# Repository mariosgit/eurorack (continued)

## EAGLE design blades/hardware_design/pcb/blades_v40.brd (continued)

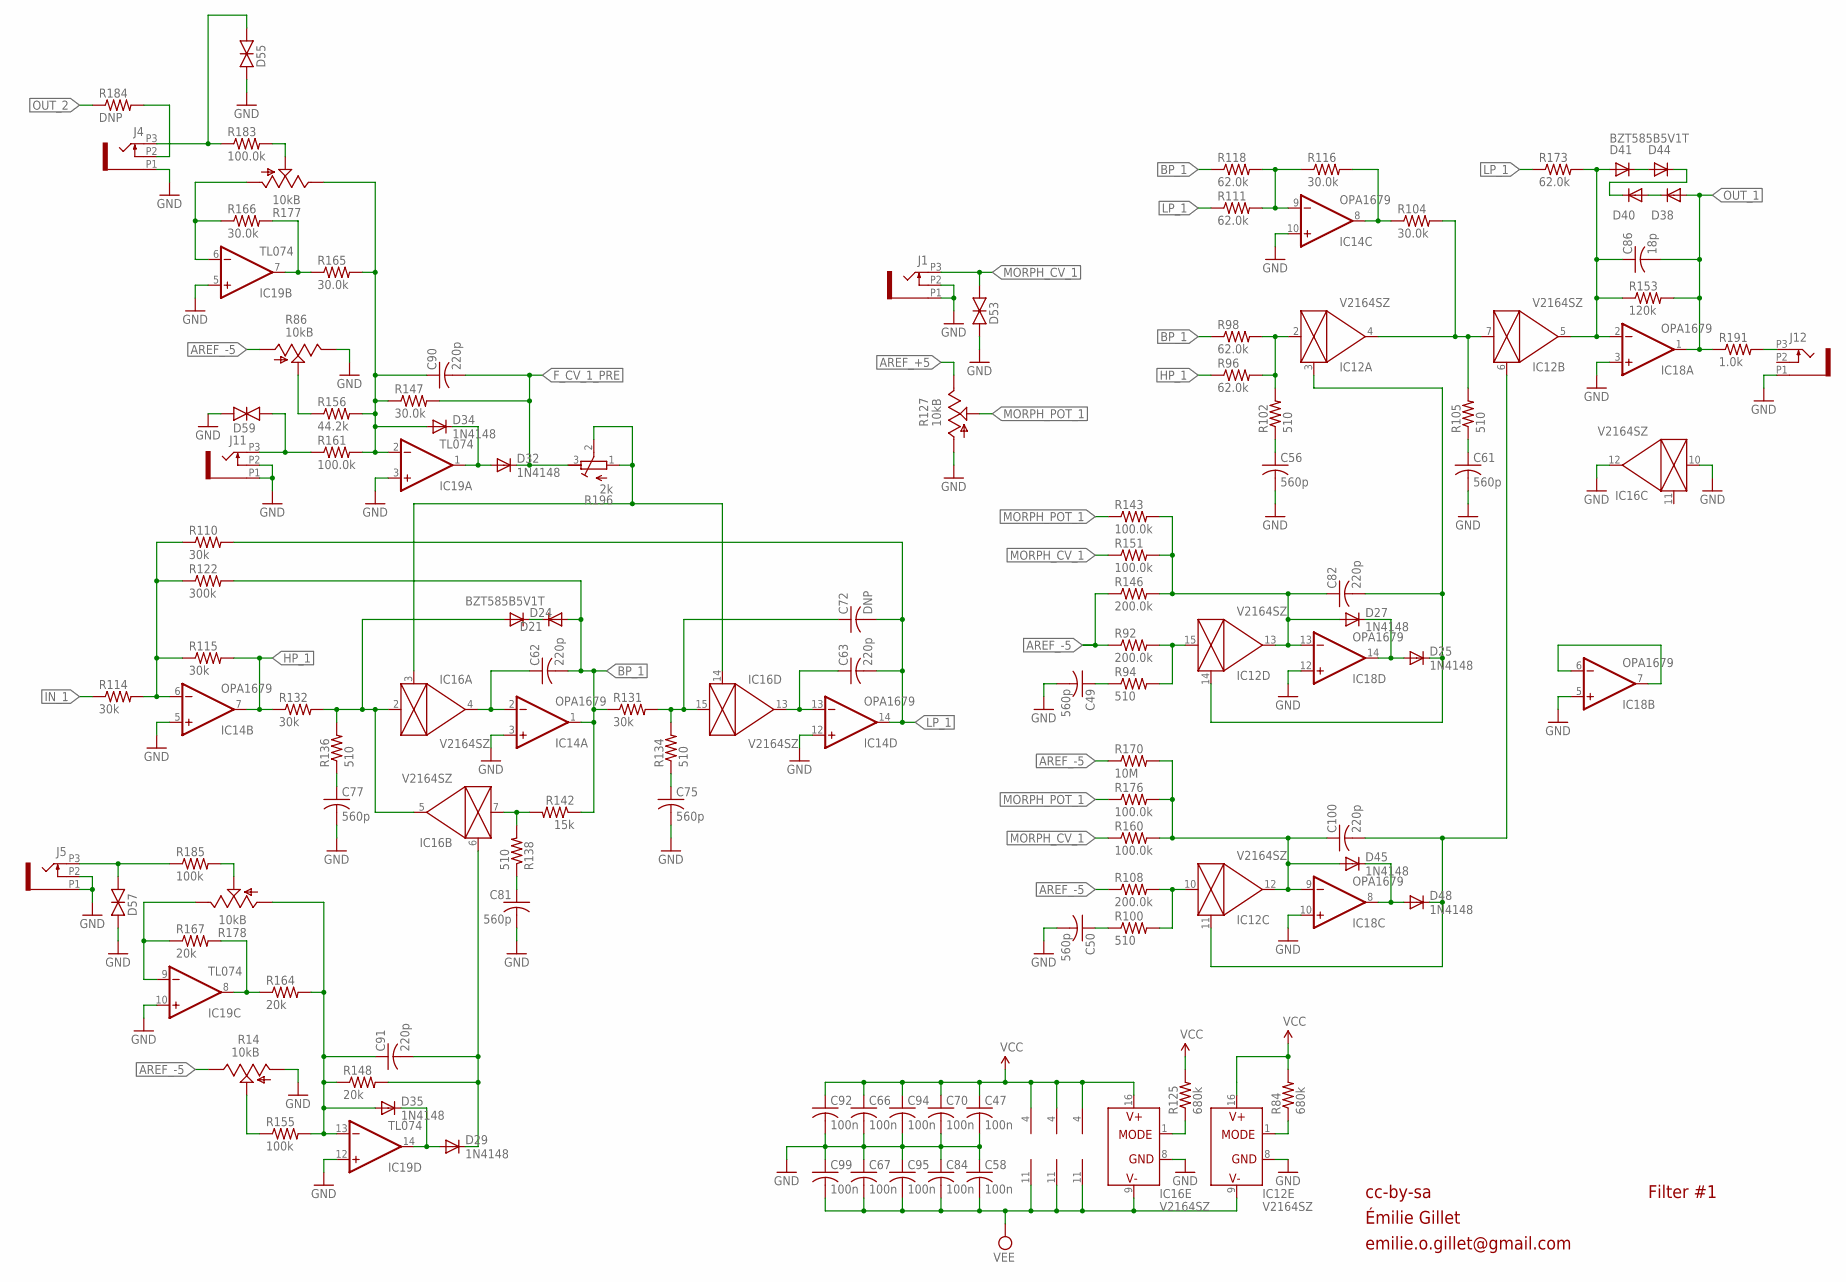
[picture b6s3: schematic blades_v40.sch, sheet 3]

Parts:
C47, C58, C66, C67, C70, C84, C92, C94, C95, C99: 100n; C0402
C49, C50, C56, C61, C75, C77, C81: 560p; C0402
C62, C63, C82, C90, C91, C100: 220p; C0402
C72: DNP; C0402
C86: 18p; C0402
D21, D24, D38, D40, D41, D44: BZT585B5V1T; SOD523
D25, D27, D29, D32, D34, D35, D45, D48: 1N4148; SOD523
D53, D55, D57, D59: TVS; 0603
IC12, IC16: V2164SZ; SOIC16N
IC14, IC18: OPA1679; TSSOP14_065
IC19: TL074; TSSOP14_065
J1, J4, J5, J11, J12: PJ301_THONKICONNTME; WQP_PJ_301M_TME
R14, R86, R127: 10kB; ALPS_POT_VERTICAL_PS
R84, R125: 680k; R0402
R92, R108, R146: 200.0k; R0402
R94, R100, R102, R105, R134, R136, R138: 510; R0402
R96, R98, R111, R118, R173: 62.0k; R0402
R104, R116, R147, R165, R166: 30.0k; R0402
R110, R114, R115, R131, R132: 30k; R0402
R122: 300k; R0402
R142: 15k; R0402
R143, R151, R160, R161, R176, R183: 100.0k; R0402
R148, R164, R167: 20k; R0402
R153: 120k; R0402
R155, R185: 100k; R0402
R156: 44.2k; R0402
R170: 10M; R0402
R177, R178: 10kB; ALPS_POT_NARROW
R184: DNP; R0603
R191: 1.0k; R0603
R196: 2k; RTRIM3296W

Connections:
AREF_+5: R127.P$1 (E); also elsewhere on the board
AREF_-5: R14.P$1 (E), R86.P$3 (A), R92.1, R108.1, R146.1, R170.1; also elsewhere on the board
BP_1: C62.2, D21.A, IC14.1 (OUT), R98.1, R118.1, R122.2, R131.1, R142.1
F_CV_1: IC16.3 (CTRL), IC16.14 (CTRL), R196.1 (E), R196.2 (S)
F_CV_1_PRE: C90.2, D32.C, R147.2, R196.3 (A); also elsewhere on the board
GND: C47.2, C49.2, C50.2, C56.2, C58.1, C61.2, C66.2, C67.1, C70.2, C75.2, C77.2, C81.2, C84.1, C92.2, C94.2, C95.1, C99.1, D53.1 (A), D55.1 (A), D57.1 (A), D59.1 (A), IC12.8 (GND), IC14.3 (+IN), IC14.5 (+IN), IC14.10 (+IN), IC14.12 (+IN), IC16.8 (GND), IC16.10 (IN), IC16.12 (OUT), IC18.3 (+IN), IC18.5 (+IN), IC18.10 (+IN), IC18.12 (+IN), IC19.3 (+IN), IC19.5 (+IN), IC19.10 (+IN), IC19.12 (+IN), J1.P1 (1), J1.P2 (2), J4.P1 (1), J5.P1 (1), J5.P2 (2), J11.P1 (1), J11.P2 (2), J12.P1 (1), R14.P$3 (A), R86.P$1 (E), R127.P$3 (A); also elsewhere on the board
HP_1: IC14.7 (OUT), R96.1, R115.2, R132.1
IN_1: R114.1; also elsewhere on the board
LP_1: C63.2, C72.2, IC14.14 (OUT), R110.2, R111.1, R173.1
MORPH_1A: C82.2, D25.C, IC12.3 (CTRL), IC12.14 (CTRL)
MORPH_1B: C100.2, D48.C, IC12.6 (CTRL), IC12.11 (CTRL)
MORPH_CV_1: D53.2 (C), J1.P3 (3), R151.1, R160.1
MORPH_POT_1: R127.P$2 (S), R143.1, R176.1
unnamed: C77.1, R136.1
unnamed: J12.P3 (3), R191.2
unnamed: C90.1, D34.A, IC19.2 (-IN), R147.1, R156.2, R161.2, R165.2, R177.P$1 (E)
unnamed: C91.1, D35.A, IC19.13 (-IN), R148.1, R155.2, R164.2, R178.P$3 (A)
unnamed: D32.A, D34.C, IC19.1 (OUT)
unnamed: R86.P$2 (S), R156.1
unnamed: IC19.9 (-IN), R167.1, R178.P$1 (E)
unnamed: IC19.8 (OUT), R164.1, R167.2
unnamed: R178.P$2 (S), R185.2
unnamed: C100.1, D45.A, IC12.12 (OUT), IC18.9 (-IN), R160.2, R170.2, R176.2
unnamed: IC14.6 (-IN), R110.1, R114.2, R115.1, R122.1
unnamed: C62.1, IC14.2 (-IN), IC16.4 (OUT)
unnamed: C75.1, R134.1
unnamed: C72.1, IC16.15 (IN), R131.2, R134.2
unnamed: C63.1, IC14.13 (-IN), IC16.13 (OUT)
unnamed: C81.1, R138.1
unnamed: IC16.7 (IN), R138.2, R142.2
unnamed: D57.2 (C), J5.P3 (3), R185.1
unnamed: D29.A, D35.C, IC19.14 (OUT)
unnamed: IC18.6 (-IN), IC18.7 (OUT)
unnamed: J4.P2 (2), R184.2
unnamed: R14.P$2 (S), R155.1
unnamed: IC12.2 (IN), R96.2, R98.2, R102.2
unnamed: IC14.9 (-IN), R111.2, R116.1, R118.2
unnamed: IC14.8 (OUT), R104.1, R116.2
unnamed: IC12.4 (OUT), IC12.7 (IN), R104.2, R105.2
unnamed: C56.1, R102.1
unnamed: C61.1, R105.1
unnamed: D45.C, D48.A, IC18.8 (OUT)
unnamed: IC12.10 (IN), R100.2, R108.2
unnamed: IC19.6 (-IN), R166.1, R177.P$3 (A)
unnamed: IC19.7 (OUT), R165.1, R166.2
unnamed: R177.P$2 (S), R183.2
unnamed: D55.2 (C), J4.P3 (3), R183.1
unnamed: D59.2 (C), J11.P3 (3), R161.1
unnamed: C50.1, R100.1
unnamed: IC12.15 (IN), R92.2, R94.2
unnamed: C49.1, R94.1
unnamed: C82.1, D27.A, IC12.13 (OUT), IC18.13 (-IN), R143.2, R146.2, R151.2
unnamed: D25.A, D27.C, IC18.14 (OUT)
unnamed: IC12.1 (MODE), R84.1
unnamed: IC16.1 (MODE), R125.1
unnamed: D21.C, D24.C
unnamed: C86.1, D41.A, IC12.5 (OUT), IC18.2 (-IN), R153.1, R173.2
unnamed: D38.C, D40.A
unnamed: D24.A, IC16.2 (IN), IC16.5 (OUT), R132.2, R136.2
unnamed: D40.C, D44.C
unnamed: D41.C, D44.A
OUT_1: C86.2, D38.A, IC18.1 (OUT), R153.2, R191.1; also elsewhere on the board
OUT_2: R184.1; also elsewhere on the board
RESONANCE_SUM_1: C91.2, D29.C, IC16.6 (CTRL), R148.2
VCC: C47.1, C66.1, C70.1, C92.1, C94.1, IC12.16 (V+), IC14.4 (V+), IC16.16 (V+), IC18.4 (V+), IC19.4 (V+), R84.2, R125.2; also elsewhere on the board
VEE: C58.2, C67.2, C84.2, C95.2, C99.2, IC12.9 (V-), IC14.11 (V-), IC16.9 (V-), IC18.11 (V-), IC19.11 (V-); also elsewhere on the board

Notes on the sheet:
Filter #1
cc-by-sa
Émilie Gillet
emilie.o.gillet@gmail.com

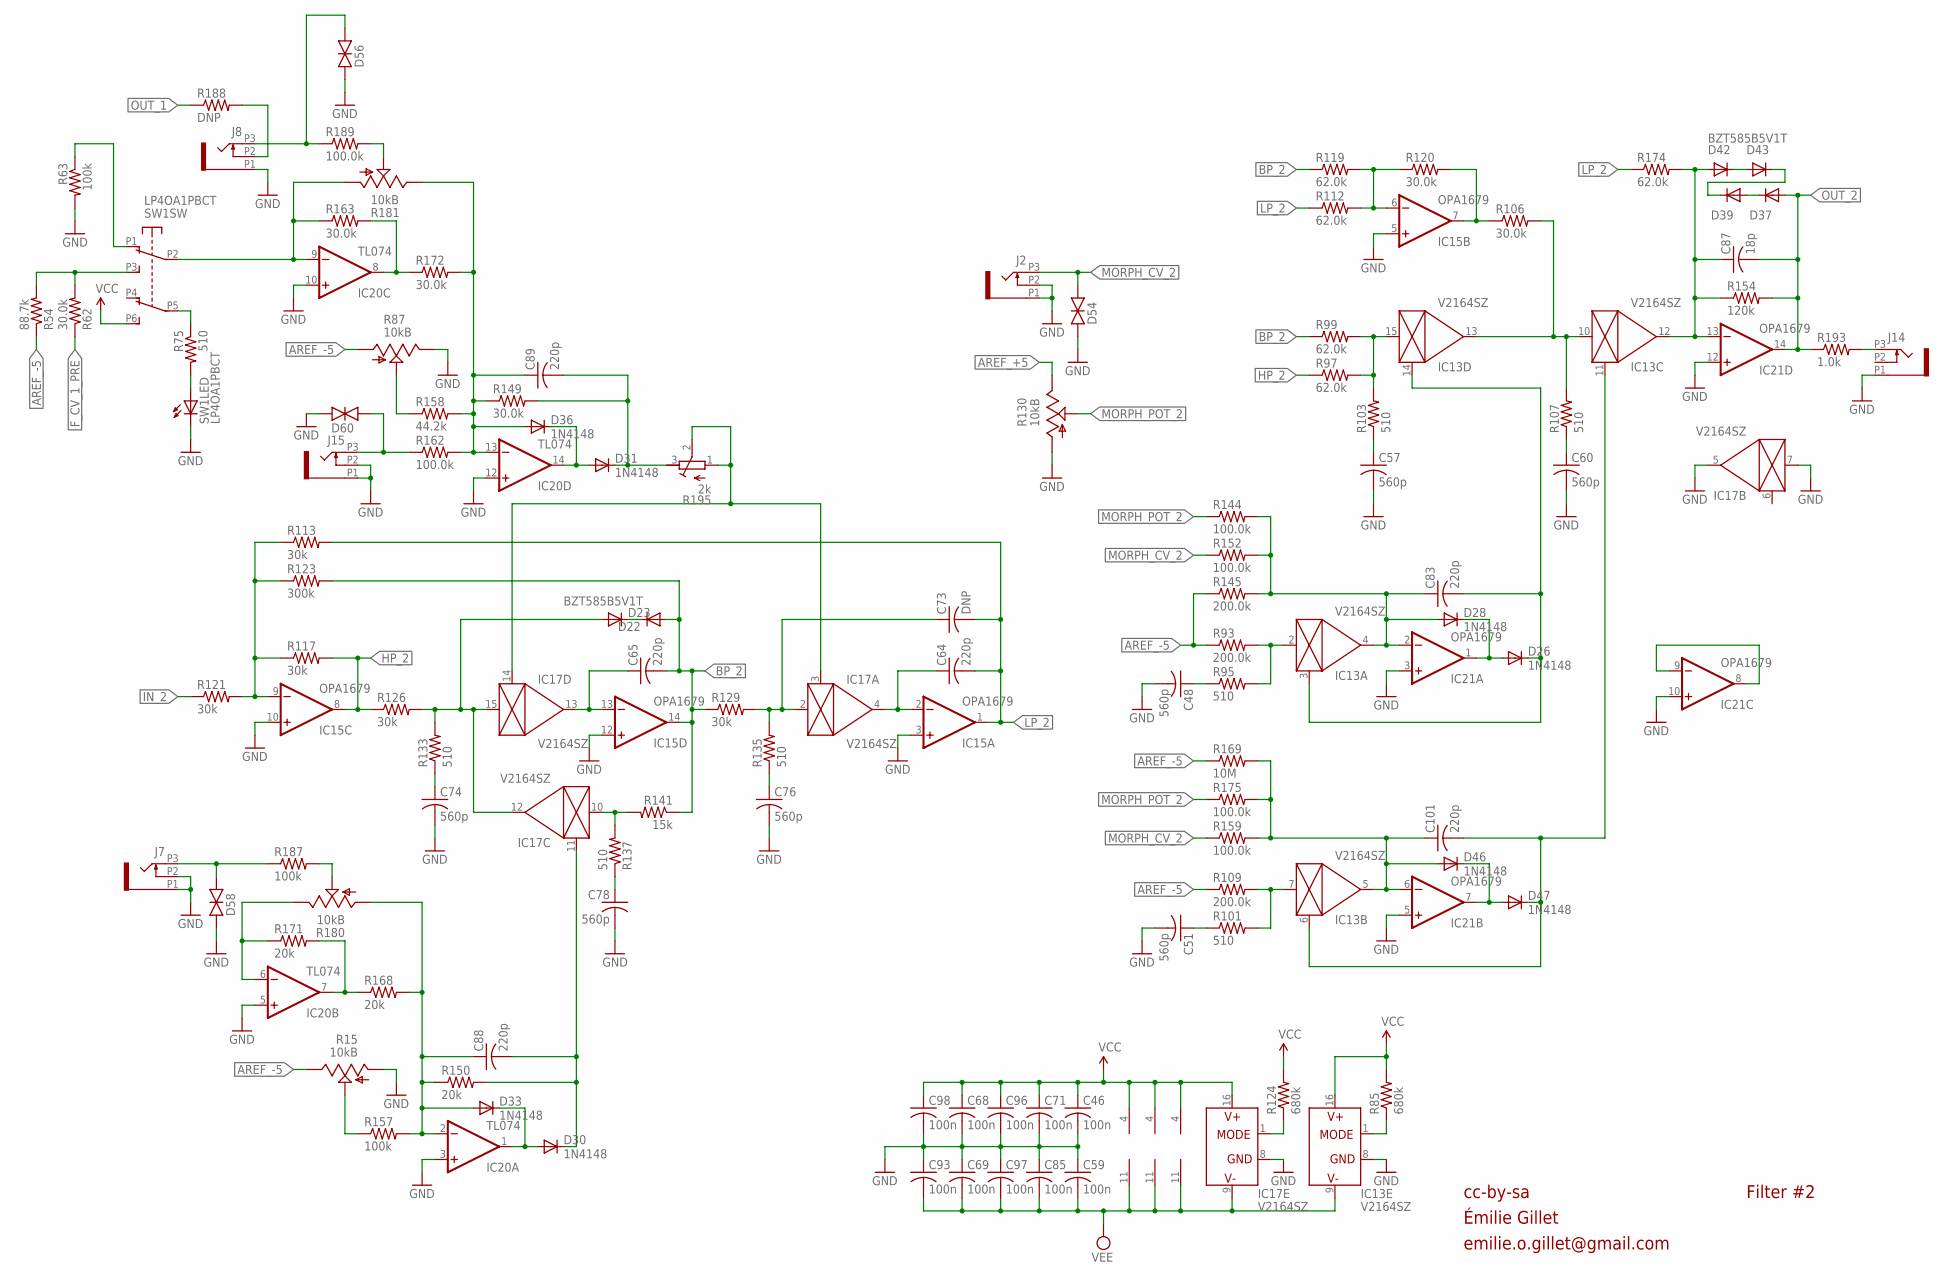
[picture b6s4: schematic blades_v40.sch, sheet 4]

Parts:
C46, C59, C68, C69, C71, C85, C93, C96, C97, C98: 100n; C0402
C48, C51, C57, C60, C74, C76, C78: 560p; C0402
C64, C65, C83, C88, C89, C101: 220p; C0402
C73: DNP; C0402
C87: 18p; C0402
D22, D23, D37, D39, D42, D43: BZT585B5V1T; SOD523
D26, D28, D30, D31, D33, D36, D46, D47: 1N4148; SOD523
D54, D56, D58, D60: TVS; 0603
IC13, IC17: V2164SZ; SOIC16N
IC15, IC21: OPA1679; TSSOP14_065
IC20: TL074; TSSOP14_065
J2, J7, J8, J14, J15: PJ301_THONKICONNTME; WQP_PJ_301M_TME
R15, R87, R130: 10kB; ALPS_POT_VERTICAL_PS
R54: 88.7k; R0402
R62, R106, R120, R149, R163, R172: 30.0k; R0402
R63, R157, R187: 100k; R0402
R75, R95, R101, R103, R107, R133, R135, R137: 510; R0402
R85, R124: 680k; R0402
R93, R109, R145: 200.0k; R0402
R97, R99, R112, R119, R174: 62.0k; R0402
R113, R117, R121, R126, R129: 30k; R0402
R123: 300k; R0402
R141: 15k; R0402
R144, R152, R159, R162, R175, R189: 100.0k; R0402
R150, R168, R171: 20k; R0402
R154: 120k; R0402
R158: 44.2k; R0402
R169: 10M; R0402
R180, R181: 10kB; ALPS_POT_NARROW
R188: DNP; R0603
R193: 1.0k; R0603
R195: 2k; RTRIM3296W
SW1: LP4OA1PBCT

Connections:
AREF_+5: R130.P$1 (E); also elsewhere on the board
AREF_-5: R15.P$1 (E), R54.1, R87.P$3 (A), R93.1, R109.1, R145.1, R169.1; also elsewhere on the board
BP_2: C65.2, D22.A, IC15.14 (OUT), R99.1, R119.1, R123.2, R129.1, R141.1
F_CV_1_PRE: R62.1; also elsewhere on the board
F_CV_2: IC17.3 (CTRL), IC17.14 (CTRL), R195.1 (E), R195.2 (S)
GND: C46.2, C48.2, C51.2, C57.2, C59.1, C60.2, C68.2, C69.1, C71.2, C74.2, C76.2, C78.2, C85.1, C93.1, C96.2, C97.1, C98.2, D54.1 (A), D56.1 (A), D58.1 (A), D60.1 (A), IC13.8 (GND), IC15.3 (+IN), IC15.5 (+IN), IC15.10 (+IN), IC15.12 (+IN), IC17.5 (OUT), IC17.7 (IN), IC17.8 (GND), IC20.3 (+IN), IC20.5 (+IN), IC20.10 (+IN), IC20.12 (+IN), IC21.3 (+IN), IC21.5 (+IN), IC21.10 (+IN), IC21.12 (+IN), J2.P1 (1), J2.P2 (2), J7.P1 (1), J7.P2 (2), J8.P1 (1), J14.P1 (1), J15.P1 (1), J15.P2 (2), R15.P$3 (A), R63.2, R87.P$1 (E), R130.P$3 (A), SW1.L2; also elsewhere on the board
HP_2: IC15.8 (OUT), R97.1, R117.2, R126.1
IN_2: R121.1; also elsewhere on the board
LP_2: C64.2, C73.2, IC15.1 (OUT), R112.1, R113.2, R174.1
MORPH_1A3: C83.2, D26.C, IC13.3 (CTRL), IC13.14 (CTRL)
MORPH_1B1: C101.2, D47.C, IC13.6 (CTRL), IC13.11 (CTRL)
MORPH_CV_2: D54.2 (C), J2.P3 (3), R152.1, R159.1
MORPH_POT_2: R130.P$2 (S), R144.1, R175.1
unnamed: IC21.8 (OUT), IC21.9 (-IN)
unnamed: R75.1, SW1.P5 (B2)
unnamed: D23.A, IC17.12 (OUT), IC17.15 (IN), R126.2, R133.2
unnamed: C89.2, D31.C, R149.2, R195.3 (A)
unnamed: J8.P2 (2), R188.2
unnamed: C87.1, D42.A, IC13.12 (OUT), IC21.13 (-IN), R154.1, R174.2
unnamed: C88.2, D30.C, IC17.11 (CTRL), R150.2
unnamed: D37.C, D39.A
unnamed: R75.2, SW1.L1
unnamed: R63.1, SW1.P1 (A1)
unnamed: C74.1, R133.1
unnamed: IC15.9 (-IN), R113.1, R117.1, R121.2, R123.1
unnamed: C65.1, IC15.13 (-IN), IC17.13 (OUT)
unnamed: C76.1, R135.1
unnamed: C73.1, IC17.2 (IN), R129.2, R135.2
unnamed: C64.1, IC15.2 (-IN), IC17.4 (OUT)
unnamed: C78.1, R137.1
unnamed: IC17.10 (IN), R137.2, R141.2
unnamed: IC13.15 (IN), R97.2, R99.2, R103.2
unnamed: IC15.6 (-IN), R112.2, R119.2, R120.1
unnamed: IC15.7 (OUT), R106.1, R120.2
unnamed: IC13.10 (IN), IC13.13 (OUT), R106.2, R107.2
unnamed: C57.1, R103.1
unnamed: C60.1, R107.1
unnamed: IC20.9 (-IN), R163.1, R181.P$3 (A), SW1.P2 (A2)
unnamed: IC20.8 (OUT), R163.2, R172.1
unnamed: R181.P$2 (S), R189.2
unnamed: D56.2 (C), J8.P3 (3), R189.1
unnamed: D60.2 (C), J15.P3 (3), R162.1
unnamed: D30.A, D33.C, IC20.1 (OUT)
unnamed: J14.P3 (3), R193.2
unnamed: R87.P$2 (S), R158.1
unnamed: IC20.6 (-IN), R171.1, R180.P$1 (E)
unnamed: IC20.7 (OUT), R168.1, R171.2
unnamed: R180.P$2 (S), R187.2
unnamed: D58.2 (C), J7.P3 (3), R187.1
unnamed: R15.P$2 (S), R157.1
unnamed: R54.2, R62.2, SW1.P3 (A3)
unnamed: C88.1, D33.A, IC20.2 (-IN), R150.1, R157.2, R168.2, R180.P$3 (A)
unnamed: C89.1, D36.A, IC20.13 (-IN), R149.1, R158.2, R162.2, R172.2, R181.P$1 (E)
unnamed: C83.1, D28.A, IC13.4 (OUT), IC21.2 (-IN), R144.2, R145.2, R152.2
unnamed: D26.A, D28.C, IC21.1 (OUT)
unnamed: C101.1, D46.A, IC13.5 (OUT), IC21.6 (-IN), R159.2, R169.2, R175.2
unnamed: D46.C, D47.A, IC21.7 (OUT)
unnamed: D31.A, D36.C, IC20.14 (OUT)
unnamed: IC13.7 (IN), R101.2, R109.2
unnamed: C51.1, R101.1
unnamed: IC13.2 (IN), R93.2, R95.2
unnamed: C48.1, R95.1
unnamed: IC13.1 (MODE), R85.1
unnamed: IC17.1 (MODE), R124.1
unnamed: D22.C, D23.C
unnamed: D42.C, D43.A
unnamed: D39.C, D43.C
OUT_1: R188.1; also elsewhere on the board
OUT_2: C87.2, D37.A, IC21.14 (OUT), R154.2, R193.1; also elsewhere on the board
VCC: C46.1, C68.1, C71.1, C96.1, C98.1, IC13.16 (V+), IC15.4 (V+), IC17.16 (V+), IC20.4 (V+), IC21.4 (V+), R85.2, R124.2, SW1.P6 (B3); also elsewhere on the board
VEE: C59.2, C69.2, C85.2, C93.2, C97.2, IC13.9 (V-), IC15.11 (V-), IC17.9 (V-), IC20.11 (V-), IC21.11 (V-); also elsewhere on the board

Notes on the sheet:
Filter #2
cc-by-sa
Émilie Gillet
emilie.o.gillet@gmail.com

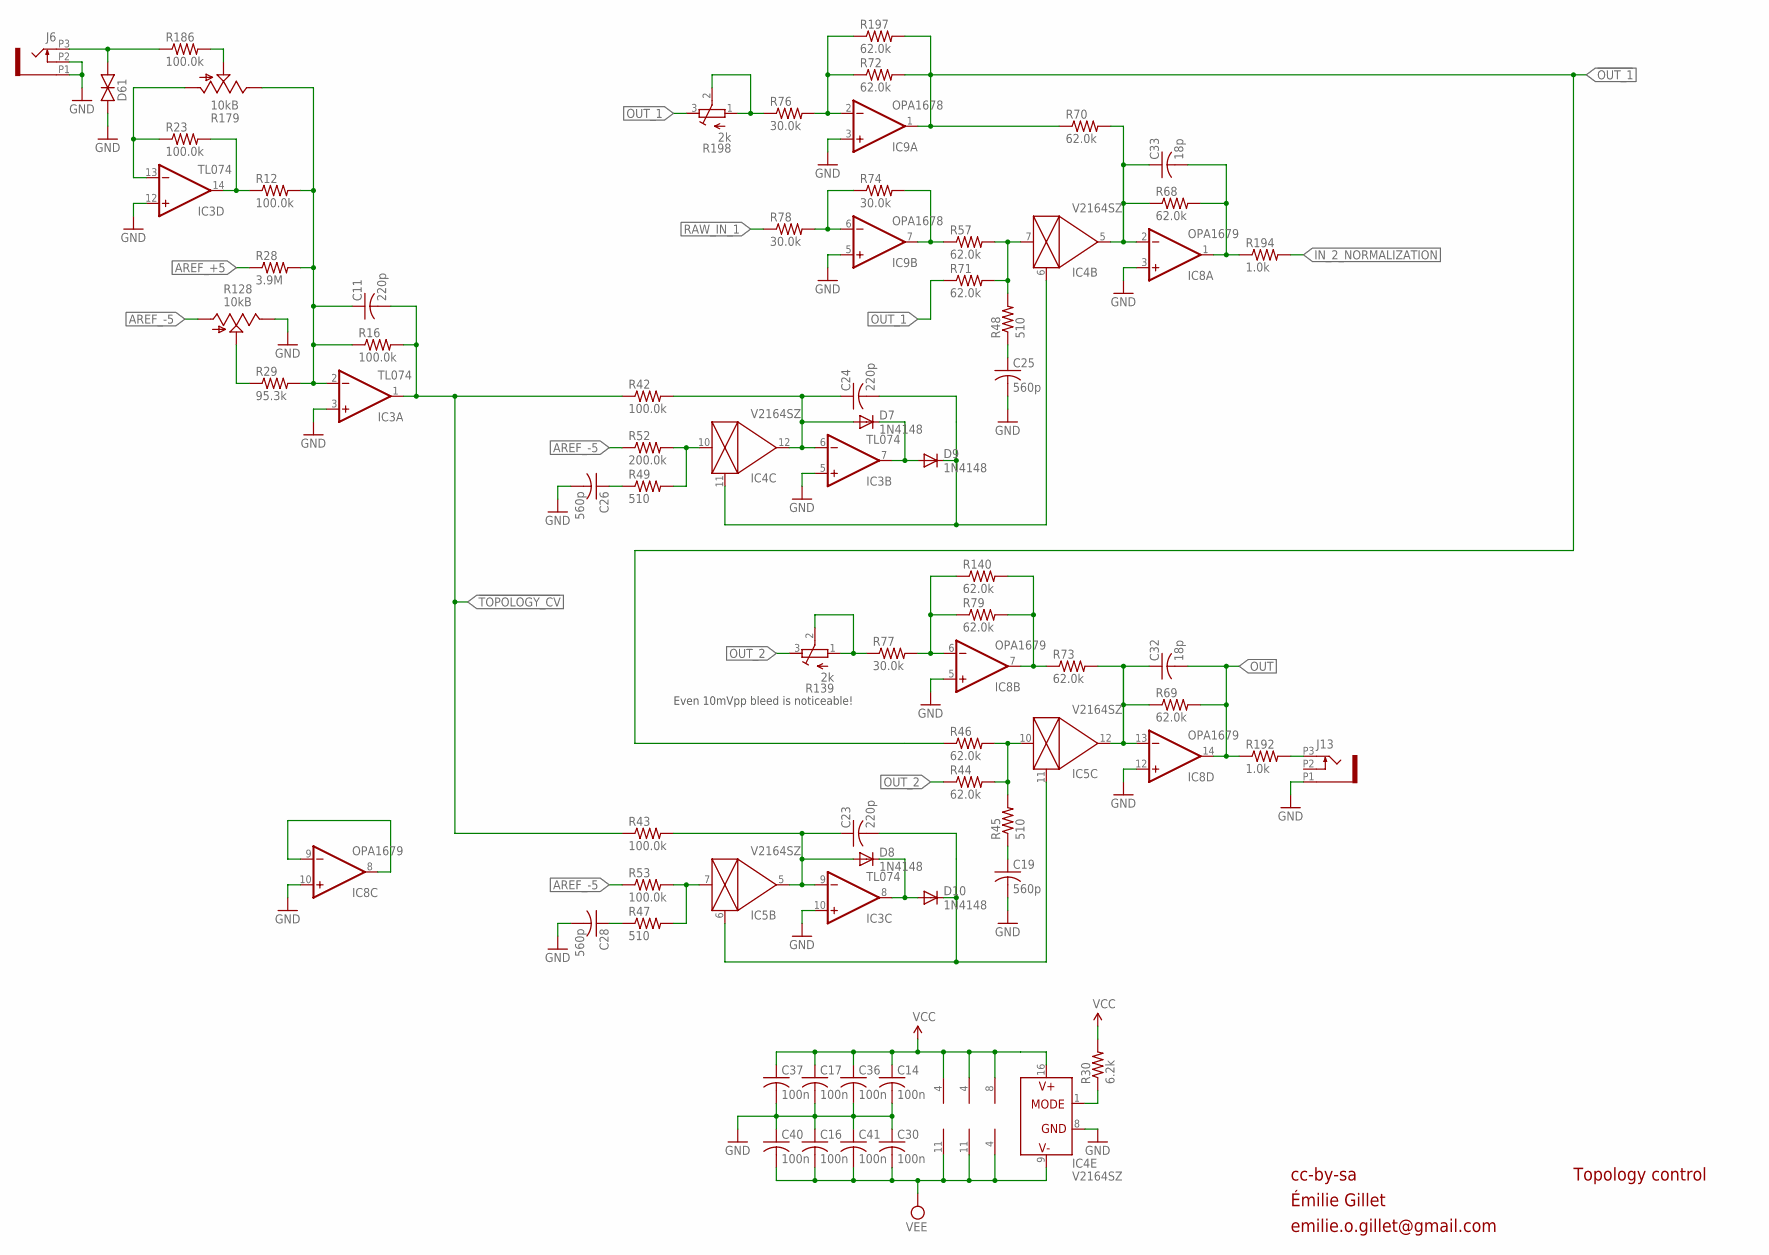
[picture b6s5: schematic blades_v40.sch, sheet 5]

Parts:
C11, C23, C24: 220p; C0402
C14, C16, C17, C30, C36, C37, C40, C41: 100n; C0402
C19, C25, C26, C28: 560p; C0402
C32, C33: 18p; C0402
D7, D8, D9, D10: 1N4148; SOD523
D61: TVS; 0603
IC3: TL074; TSSOP14_065
IC4, IC5: V2164SZ; SOIC16N
IC8: OPA1679; TSSOP14_065
IC9: OPA1678; VSSOP8
J6, J13: PJ301_THONKICONNTME; WQP_PJ_301M_TME
R12, R16, R23, R42, R43, R53, R186: 100.0k; R0402
R28: 3.9M; R0402
R29: 95.3k; R0402
R30: 6.2k; R0402
R44, R46, R57, R68, R69, R70, R71, R72, R73, R79, R140, R197: 62.0k; R0402
R45, R47, R48, R49: 510; R0402
R52: 200.0k; R0402
R74, R76, R77, R78: 30.0k; R0402
R128: 10kB; ALPS_POT_VERTICAL_PS
R139, R198: 2k; RTRIM3296W
R179: 10kB; ALPS_POT_NARROW
R192, R194: 1.0k; R0603

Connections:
!OUT_1: IC9.1 (OUT), R46.1, R70.1, R72.2, R197.2
!TOPOLOGY_CV: C11.2, IC3.1 (OUT), R16.2, R42.1, R43.1
AREF_+5: R28.1; also elsewhere on the board
AREF_-5: R52.1, R53.1, R128.P$3 (A); also elsewhere on the board
F1: C24.2, D9.C, IC4.6 (CTRL), IC4.11 (CTRL)
F2: C23.2, D10.C, IC5.6 (CTRL), IC5.11 (CTRL)
F_CV_3: R77.1, R139.1 (E), R139.2 (S)
GND: C14.2, C16.1, C17.2, C19.2, C25.2, C26.2, C28.2, C30.1, C36.2, C37.2, C40.1, C41.1, D61.1 (A), IC3.3 (+IN), IC3.5 (+IN), IC3.10 (+IN), IC3.12 (+IN), IC4.8 (GND), IC8.3 (+IN), IC8.5 (+IN), IC8.10 (+IN), IC8.12 (+IN), IC9.3 (+IN), IC9.5 (+IN), J6.P1 (1), J6.P2 (2), J13.P1 (1), R128.P$1 (E); also elsewhere on the board
IN_2_NORMALIZATION: R194.2; also elsewhere on the board
unnamed: IC9.6 (-IN), R74.1, R78.2
unnamed: IC5.10 (IN), R44.2, R45.2, R46.2
unnamed: IC8.6 (-IN), R77.2, R79.1, R140.1
unnamed: IC8.7 (OUT), R73.1, R79.2, R140.2
unnamed: IC9.7 (OUT), R57.1, R74.2
unnamed: IC4.7 (IN), R48.2, R57.2, R71.2
unnamed: C32.1, IC5.12 (OUT), IC8.13 (-IN), R69.1, R73.2
unnamed: C19.1, R45.1
unnamed: IC9.2 (-IN), R72.1, R76.2, R197.1
unnamed: C25.1, R48.1
unnamed: C33.1, IC4.5 (OUT), IC8.2 (-IN), R68.1, R70.2
unnamed: C23.1, D8.A, IC3.9 (-IN), IC5.5 (OUT), R43.2
unnamed: IC4.10 (IN), R49.2, R52.2
unnamed: J13.P3 (3), R192.2
unnamed: D8.C, D10.A, IC3.8 (OUT)
unnamed: C26.1, R49.1
unnamed: IC8.8 (OUT), IC8.9 (-IN)
unnamed: C11.1, IC3.2 (-IN), R12.2, R16.1, R28.2, R29.2, R179.P$1 (E)
unnamed: D61.2 (C), J6.P3 (3), R186.1
unnamed: R29.1, R128.P$2 (S)
unnamed: C24.1, D7.A, IC3.6 (-IN), IC4.12 (OUT), R42.2
unnamed: D7.C, D9.A, IC3.7 (OUT)
unnamed: IC5.7 (IN), R47.2, R53.2
unnamed: C28.1, R47.1
unnamed: R179.P$2 (S), R186.2
unnamed: IC3.14 (OUT), R12.1, R23.2
unnamed: IC3.13 (-IN), R23.1, R179.P$3 (A)
unnamed: R76.1, R198.1 (E), R198.2 (S)
unnamed: IC4.1 (MODE), R30.1
OUT: C32.2, IC8.14 (OUT), R69.2, R192.1
OUT_1: R71.1, R198.3 (A); also elsewhere on the board
OUT_2: R44.1, R139.3 (A); also elsewhere on the board
RAW_IN_1: R78.1; also elsewhere on the board
VCC: C14.1, C17.1, C36.1, C37.1, IC3.4 (V+), IC4.16 (V+), IC8.4 (V+), IC9.8 (V+), R30.2; also elsewhere on the board
VEE: C16.2, C30.2, C40.2, C41.2, IC3.11 (V-), IC4.9 (V-), IC8.11 (V-), IC9.4 (V-); also elsewhere on the board
ZZZZ: C33.2, IC8.1 (OUT), R68.2, R194.1

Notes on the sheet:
Topology control
Even 10mVpp bleed is noticeable!
cc-by-sa
Émilie Gillet
emilie.o.gillet@gmail.com

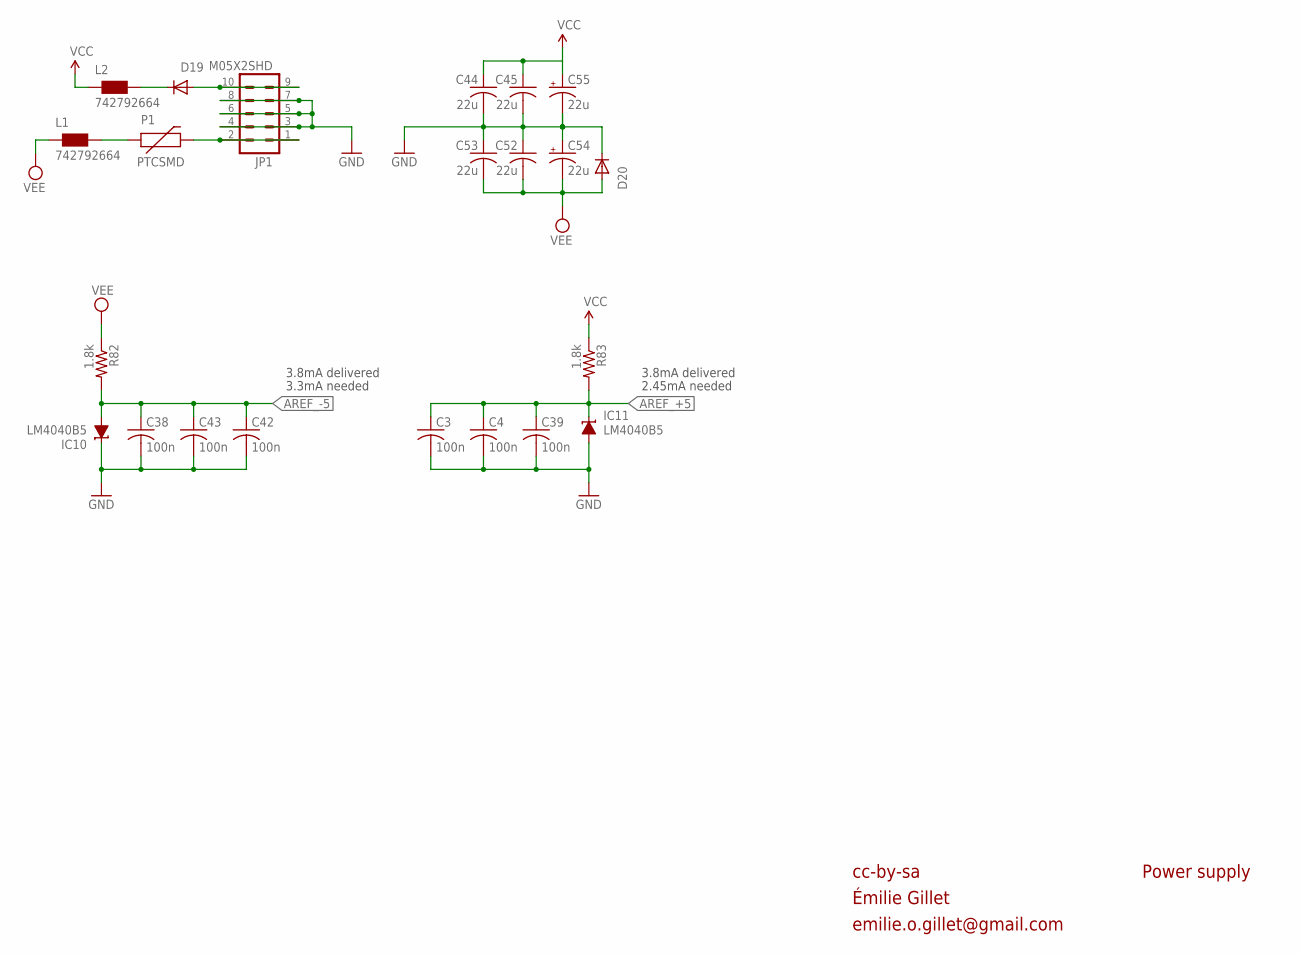
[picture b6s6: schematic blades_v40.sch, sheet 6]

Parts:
C3, C4, C38, C39, C42, C43: 100n; C0402
C44, C45, C52, C53: 22u; C1206
C54, C55: 22u; PANASONIC_B
D19, D20: 1N5819HW; SOD123
IC10, IC11: LM4040B5; DBZ_R-PDSO-G3
JP1: M05X2SHD; 2X5-SHROUDED
L1, L2: 742792664; 0603
P1: PTCSMD; PTC-1206
R82, R83: 1.8k; R0402

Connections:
AREF_+5: C3.1, C4.1, C39.1, IC11.1 (C), R83.2; also elsewhere on the board
AREF_-5: C38.1, C42.1, C43.1, IC10.2 (A), R82.2; also elsewhere on the board
GND: C3.2, C4.2, C38.2, C39.2, C42.2, C43.2, C44.2, C45.2, C52.1, C53.1, C54.+, C55.-, D20.C, IC10.1 (C), IC11.2 (A), JP1.3, JP1.4, JP1.5, JP1.6, JP1.7, JP1.8; also elsewhere on the board
unnamed: JP1.1, JP1.2, P1.2
unnamed: D19.A, JP1.9, JP1.10
unnamed: L1.2, P1.1
unnamed: D19.C, L2.2
VCC: C44.1, C45.1, C55.+, L2.1, R83.1; also elsewhere on the board
VEE: C52.2, C53.2, C54.-, D20.A, L1.1, R82.1; also elsewhere on the board

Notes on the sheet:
Power supply
3.3mA needed
2.45mA needed
3.8mA delivered
cc-by-sa
Émilie Gillet
emilie.o.gillet@gmail.com

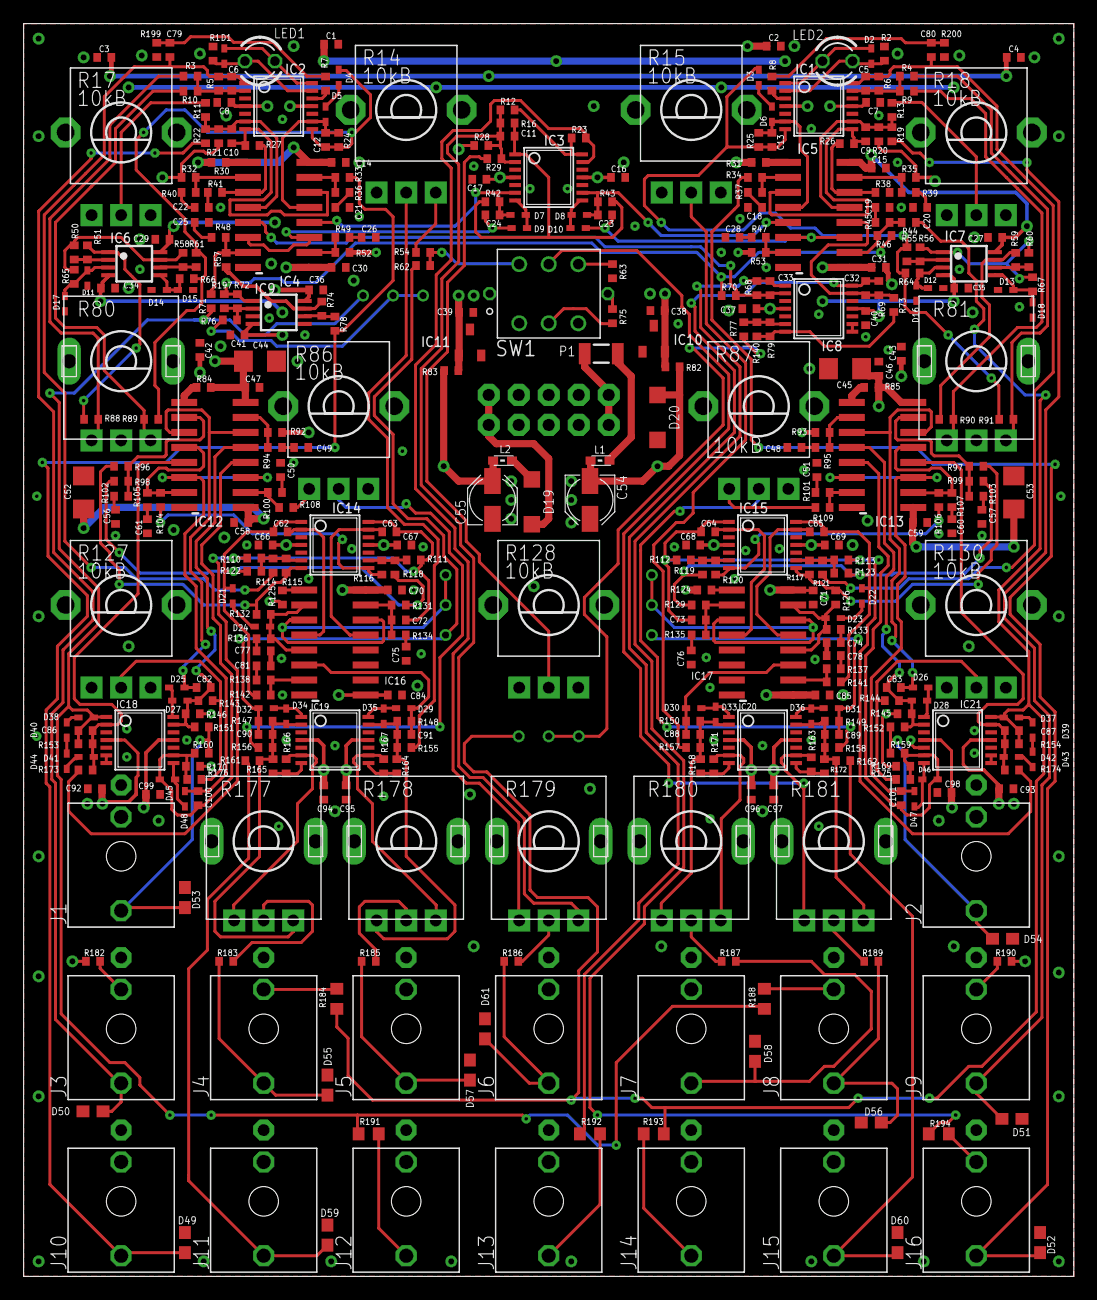
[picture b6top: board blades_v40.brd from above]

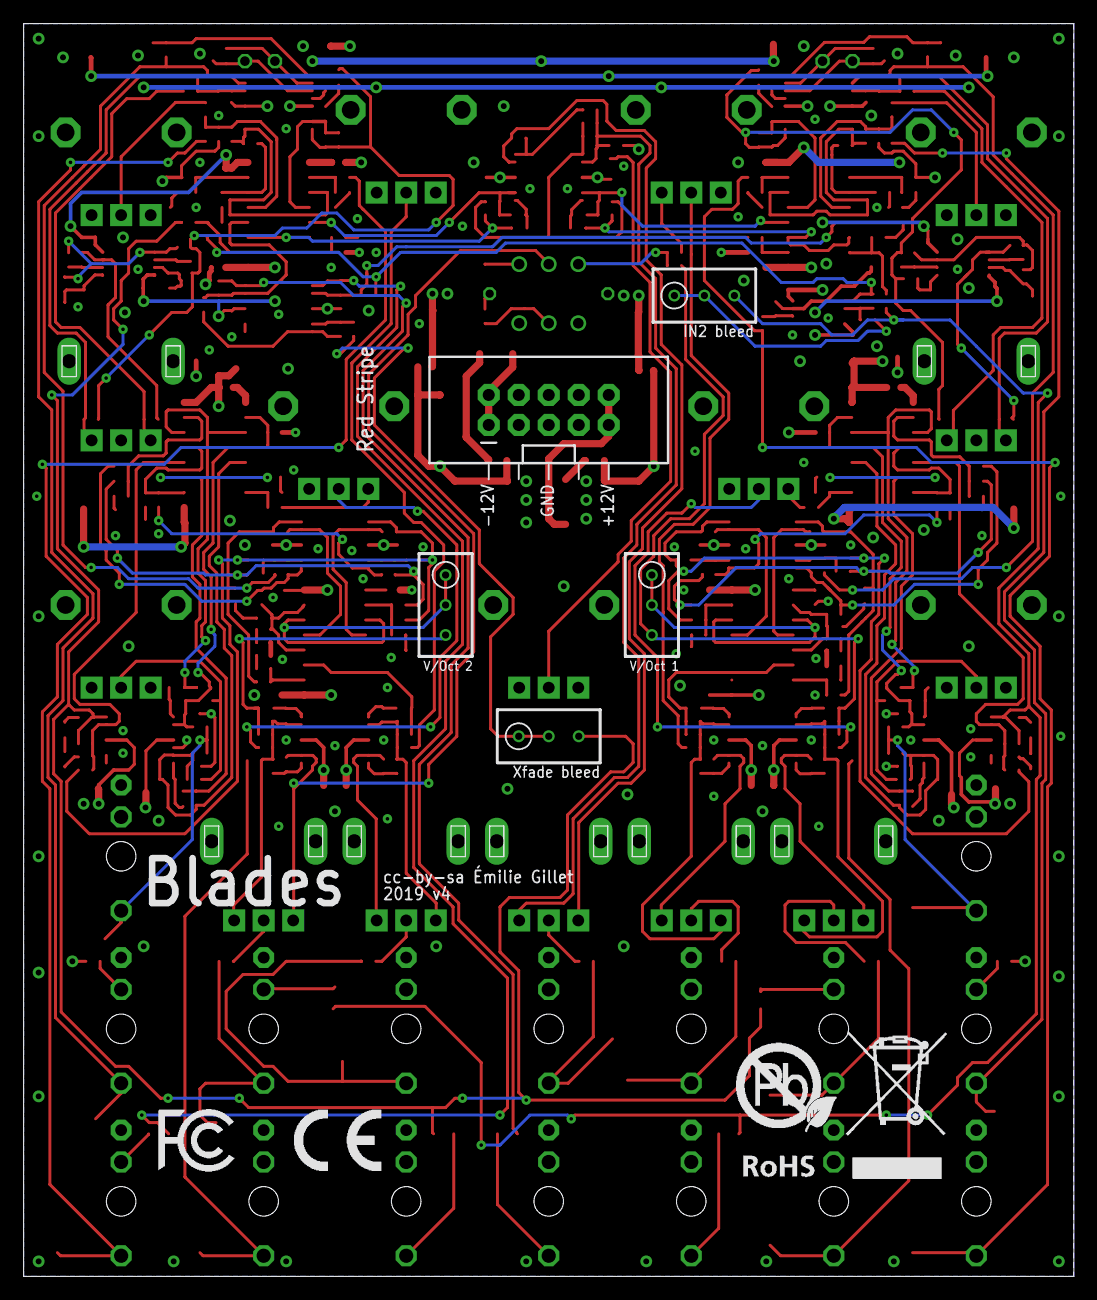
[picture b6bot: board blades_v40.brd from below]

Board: 4 copper layers, 88.9 x 106.0 mm, 409 parts (8 on the bottom side), 225 nets.

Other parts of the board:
U$1: ROHS_BIG
U$2: FCC_MEDIUM
U$3: CE_MEDIUM

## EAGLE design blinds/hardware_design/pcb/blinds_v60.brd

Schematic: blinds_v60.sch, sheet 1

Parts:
C6, C9, C10: 47p; C0603
C12, C13: 560p; C0603
IC1, IC2: OPA4171; TSSOP14
IC3: V2164SZ; SOIC16N
J1, J2, J3: PJ301_THONKICONN6; WQP_PJ_301M6
LED1: WP7113SRSGW; LED5MM
LED2: WP937EGW; LED3MM
R1: 205.0k; R0603
R2, R6, R9, R11: 100k; R0603
R3, R16, R19, R20, R28: 100.0k; R0603
R4: 10kB; ALPS_POT_VERTICAL_PS
R5: 10kB; ALPS_POT_VERTICAL
R7, R8, R13: 4.30k; R0603
R10: 3.90k; R0603
R12, R18, R22, R24: 1.0M; R0603
R14: 66.50k; R0603
R15, R21: 1.2k; R0603
R17: 402; R0603
R23, R29: 33.20k; R0603
R26, R27: 510; R0603

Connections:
1_TO_2: IC1.14 (OUT), R8.1; also elsewhere on the board
AREF_+10: R1.2, R3.1, R20.2; also elsewhere on the board
AREF_-10: R16.2, R28.2; also elsewhere on the board
CV_IN_1: J3.P3 (3), R11.2
FOO: IC3.2 (IN), R27.2, R28.1
GAIN_1: C6.1, IC2.1 (OUT), R6.1, R22.2, R23.2, R29.2
GND: C12.2, C13.2, IC1.3 (+IN), IC1.5 (+IN), IC1.12 (+IN), IC2.3 (+IN), IC2.5 (+IN), IC2.12 (+IN), J1.P1 (1), J2.P1 (1), J3.P1 (1), J3.P2 (2), R4.P$3 (A), R12.2, R15.2, R18.2, R21.2; also elsewhere on the board
unnamed: R4.P$2 (S), R16.1
unnamed: IC1.2 (-IN), IC3.13 (OUT), R7.2
unnamed: IC2.8 (OUT), LED2.K (C)
unnamed: IC2.13 (-IN), R5.P$1 (E), R9.2
unnamed: J2.P3 (3), R17.1
unnamed: IC2.14 (OUT), R2.2, R9.1
unnamed: C6.2, IC2.2 (-IN), R1.1, R2.1, R4.P$1 (E), R5.P$3 (A), R6.2
unnamed: C9.1, IC1.6 (-IN), R13.1, R14.2, R23.1
unnamed: R5.P$2 (S), R11.1
unnamed: IC2.9 (-IN), LED2.A, R21.1
unnamed: IC1.8 (OUT), LED1.K (C)
unnamed: IC1.9 (-IN), LED1.A, R15.1
unnamed: C13.1, R27.1
unnamed: J1.P3 (3), R19.2
unnamed: IC1.13 (-IN), R8.2, R10.1
unnamed: J2.P2 (2), R10.2
unnamed: C12.1, R26.1
unnamed: J1.P2 (2), R3.2
unnamed: IC1.1 (OUT), R7.1, R13.2
unnamed: C10.1, IC2.6 (-IN), IC3.4 (OUT), R19.1, R20.1
unnamed: C10.2, IC2.7 (OUT), IC3.3 (CTRL), IC3.14 (CTRL)
unnamed: IC3.15 (IN), R26.2, R29.1
unnamed: IC1.10 (+IN), R18.1, R24.1
unnamed: IC2.10 (+IN), R12.1, R22.1
OUT1: C9.2, IC1.7 (OUT), R14.1, R17.2, R24.2

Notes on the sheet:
cc-by-sa
Émilie Gillet
emilie.o.gillet@gmail.com
Channel 1

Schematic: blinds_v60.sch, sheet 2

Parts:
C14, C15: 560p; C0603
C19, C20, C23: 47p; C0603
IC3: V2164SZ; SOIC16N
IC4, IC5: OPA4171; TSSOP14
J4, J5, J6: PJ301_THONKICONN6; WQP_PJ_301M6
LED3: WP7113SRSGW; LED5MM
LED4: WP937EGW; LED3MM
R30, R54: 33.20k; R0603
R31, R34, R38, R39, R49: 100.0k; R0603
R32, R33: 510; R0603
R35, R42, R52, R58: 1.0M; R0603
R36: 10kB; ALPS_POT_VERTICAL_PS
R37: 10kB; ALPS_POT_VERTICAL
R40, R41, R46: 4.30k; R0603
R43, R45, R50, R51: 100k; R0603
R44: 3.90k; R0603
R47, R56: 66.50k; R0603
R48, R53: 1.2k; R0603
R55: 402; R0603
R57: 205.0k; R0603

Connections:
1_TO_2: R56.2; also elsewhere on the board
2_TO_3: IC4.14 (OUT), R41.1; also elsewhere on the board
AREF_+10: R34.1, R38.2, R57.2; also elsewhere on the board
AREF_-10: R31.2, R49.2; also elsewhere on the board
FOO1: IC3.7 (IN), R31.1, R33.2
GAIN_2: C23.1, IC5.7 (OUT), R30.2, R42.2, R51.1, R54.2
GND: C14.2, C15.2, IC4.3 (+IN), IC4.5 (+IN), IC4.12 (+IN), IC5.3 (+IN), IC5.5 (+IN), IC5.12 (+IN), J4.P1 (1), J5.P1 (1), J6.P1 (1), J6.P2 (2), R35.2, R36.P$3 (A), R48.2, R52.2, R53.2; also elsewhere on the board
unnamed: J5.P3 (3), R55.1
unnamed: C15.1, R32.1
unnamed: IC3.10 (IN), R30.1, R32.2
unnamed: IC3.12 (OUT), IC4.2 (-IN), R40.2
unnamed: C20.1, IC4.6 (-IN), R46.1, R47.2, R54.1, R56.1
unnamed: J6.P3 (3), R45.2
unnamed: IC5.13 (-IN), R37.P$1 (E), R43.2
unnamed: IC5.14 (OUT), R43.1, R50.2
unnamed: C23.2, IC5.6 (-IN), R36.P$1 (E), R37.P$3 (A), R50.1, R51.2, R57.1
unnamed: R36.P$2 (S), R49.1
unnamed: IC5.8 (OUT), LED4.K (C)
unnamed: IC5.9 (-IN), LED4.A, R53.1
unnamed: IC4.8 (OUT), LED3.K (C)
unnamed: IC4.9 (-IN), LED3.A, R48.1
unnamed: IC4.13 (-IN), R41.2, R44.1
unnamed: J5.P2 (2), R44.2
unnamed: IC4.1 (OUT), R40.1, R46.2
unnamed: R37.P$2 (S), R45.1
unnamed: C14.1, R33.1
unnamed: C19.1, IC3.5 (OUT), IC5.2 (-IN), R38.1, R39.1
unnamed: C19.2, IC3.6 (CTRL), IC3.11 (CTRL), IC5.1 (OUT)
unnamed: J4.P3 (3), R39.2
unnamed: J4.P2 (2), R34.2
unnamed: IC4.10 (+IN), R52.1, R58.1
unnamed: IC5.10 (+IN), R35.1, R42.1
OUT2: C20.2, IC4.7 (OUT), R47.1, R55.2, R58.2

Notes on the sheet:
cc-by-sa
Channel 2
Émilie Gillet
emilie.o.gillet@gmail.com
